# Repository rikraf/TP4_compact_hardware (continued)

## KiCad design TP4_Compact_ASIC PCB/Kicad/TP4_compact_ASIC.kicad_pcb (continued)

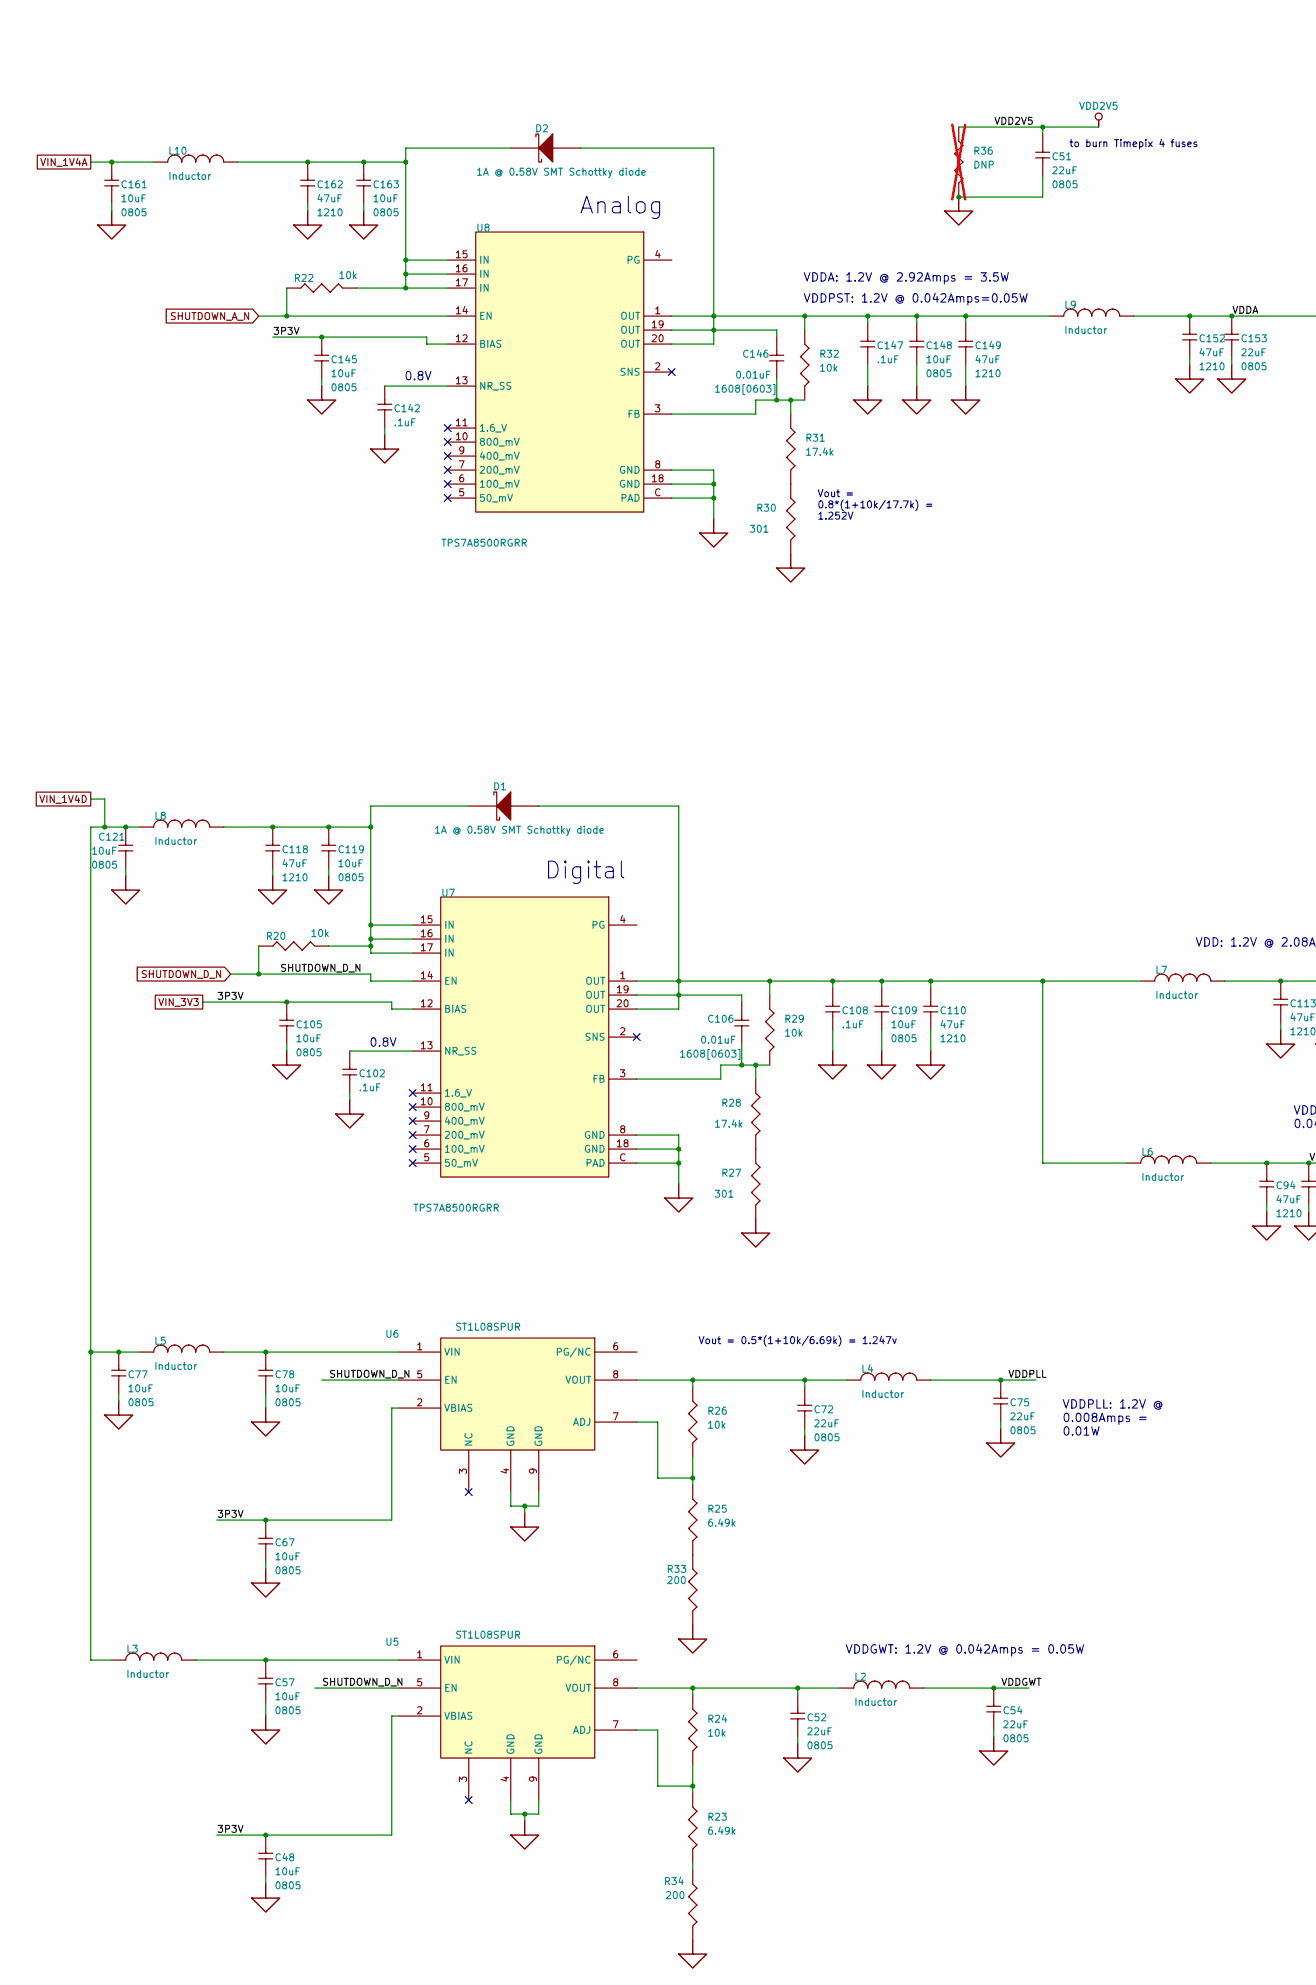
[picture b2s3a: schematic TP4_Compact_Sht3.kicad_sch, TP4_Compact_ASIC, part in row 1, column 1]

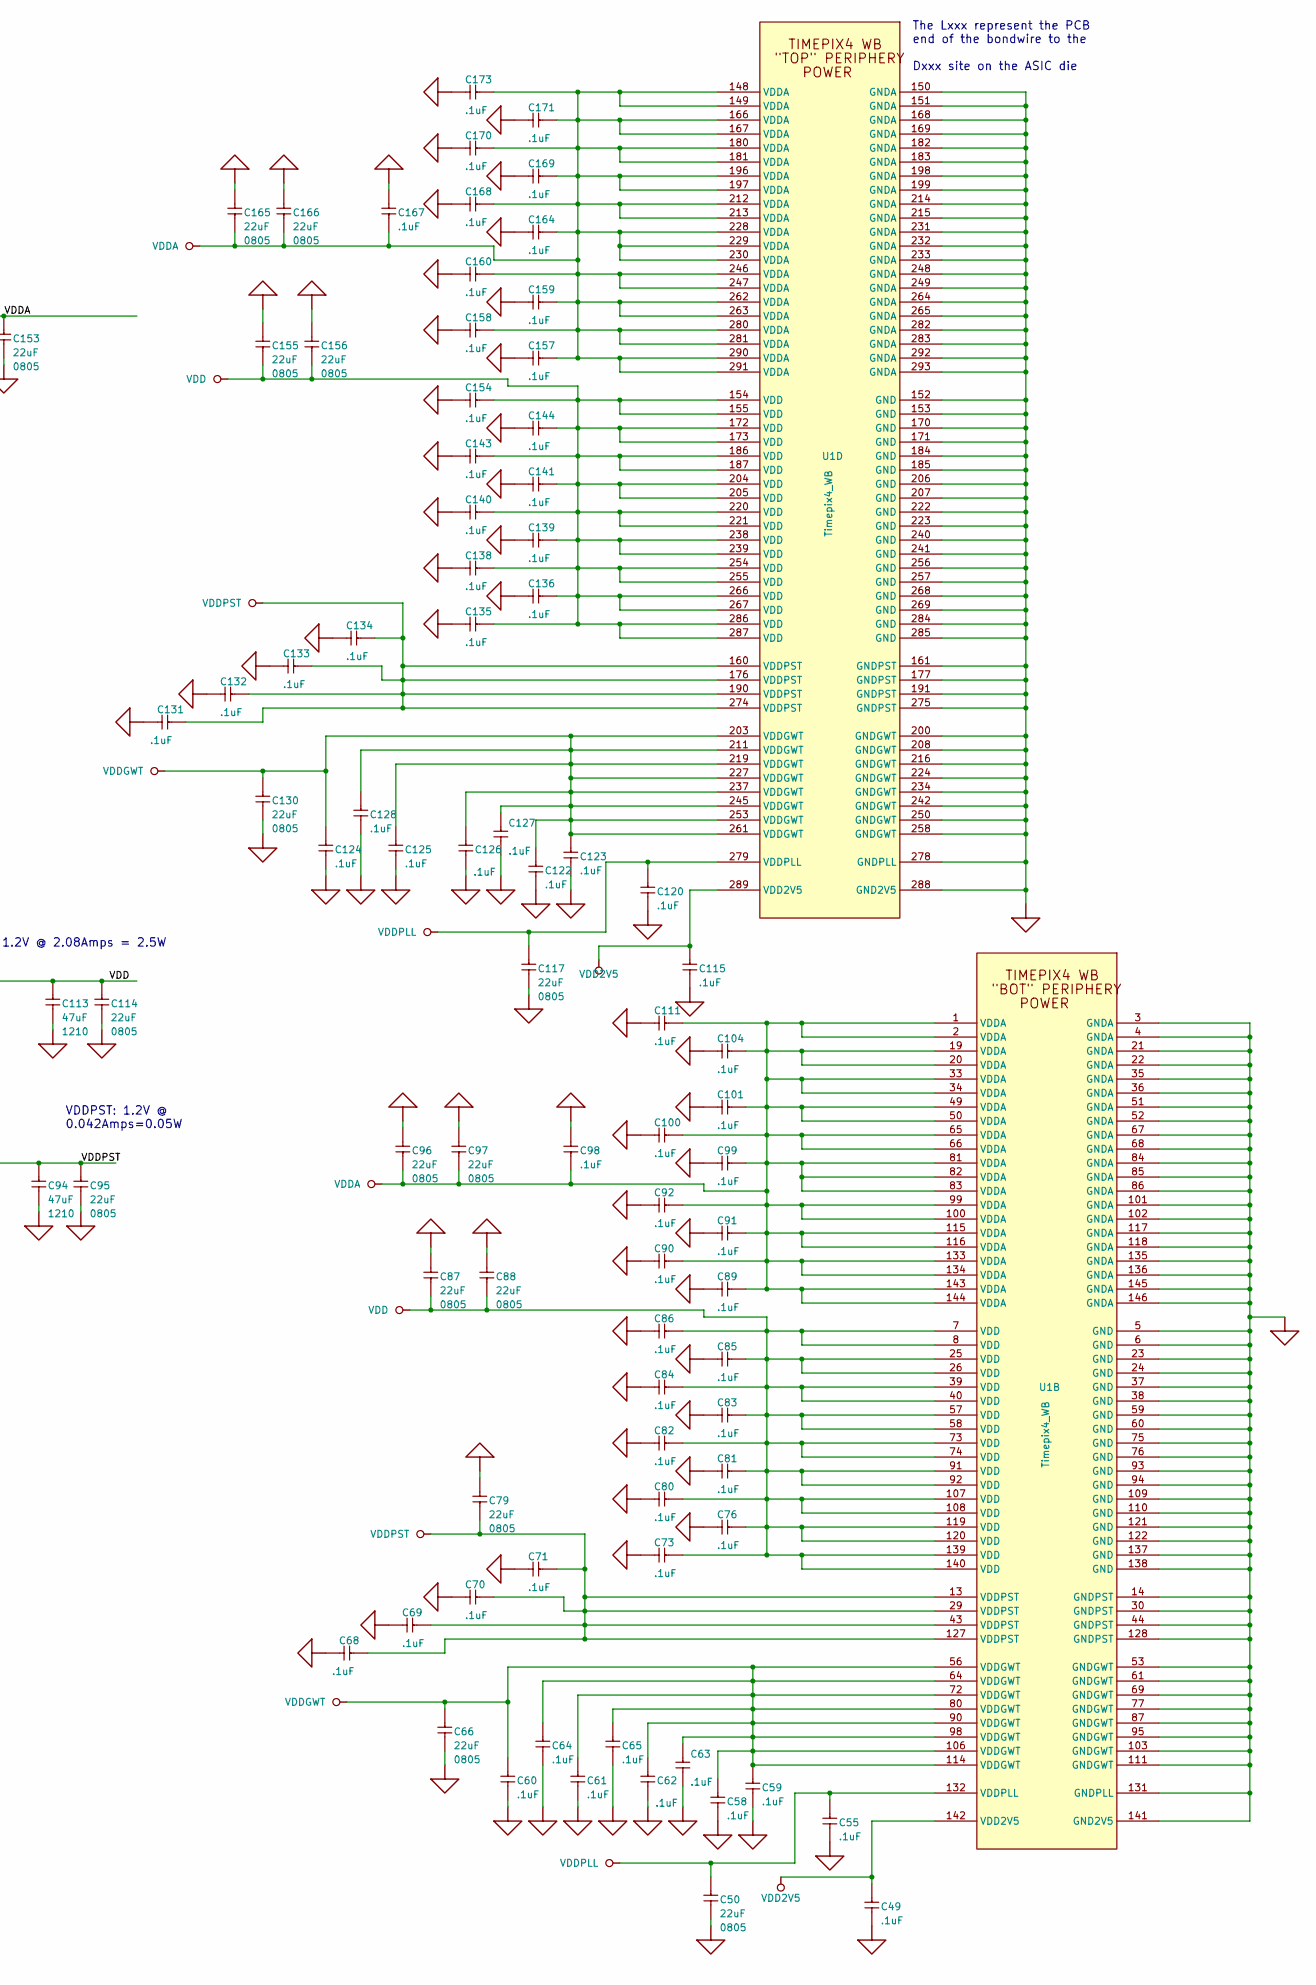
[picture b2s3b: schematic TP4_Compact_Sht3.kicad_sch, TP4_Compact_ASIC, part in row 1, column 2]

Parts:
C48, C57, C67, C77, C78, C105, C109, C119, C121, C145, C148, C161, C163: 10uF; C0805; VOLTAGE - RATED 10V; TOLERANCE ±10%; MANUFACTURER PART NUMBER GCM21BR70J106KE22L
C49, C55, C58, C59, C60, C61, C62, C63, C64, C65, C68, C69, C70, C71, C73, C76, C80, C81, C82, C83, C84, C85, C86, C89, C90, C91, C92, C98, C99, C100, C101, C102, C104, C108, C111, C115, C120, C122, C123, C124, C125, C126, C127, C128, C131, C132, C133, C134, C135, C136, C138, C139, C140, C141, C142, C143, C144, C147, C154, C157, C158, C159, C160, C164, C167, C168, C169, C170, C171, C173: .1uF; C_0201_0603Metric; VOLTAGE - RATED 6.3V; TOLERANCE ±10%; MANUFACTURER PART NUMBER GRM033R61A104ME15D
C50, C51, C52, C54, C66, C72, C75, C79, C87, C88, C95, C96, C97, C114, C117, C130, C153, C155, C156, C165, C166: 22uF; C0805; VOLTAGE - RATED 10V; TOLERANCE ±10%; MANUFACTURER PART NUMBER CL21X226MQQNNNG
C94, C110, C113, C118, C149, C152, C162: 47uF; C1210_M; VOLTAGE - RATED 10V; TOLERANCE ±10%; MANUFACTURER PART NUMBER GCM32ER70J476KE19L
C106, C146: 0.01uF; 1608[0603]; VOLTAGE - RATED 10V; TOLERANCE ±10%; MANUFACTURER PART NUMBER C0603C103K5RACTU
D1, D2: 1A @ 0.58V SMT Schottky diode; DO-219AD; MANUFACTURER PART NUMBER V1PM10-M3/H
L2, L3, L4, L5, L6, L7, L8, L9, L10: Inductor; L_0805_2012Metric; CURRENT RATING 4 Amps; MANUFACTURER PART NUMBER BLM21SP181BH1D
R20, R22, R24, R26, R29, R32: 10k; R_0402_1005Metric; MANUFACTURER PART NUMBER CR0402-FX-1002GLF
R23, R25: 6.49k; R_0402_1005Metric; MANUFACTURER PART NUMBER CR0402-FX-6491GLF
R27, R30: 301; R_0402_1005Metric; MANUFACTURER PART NUMBER CR0402-FX-3010GLF
R28, R31: 17.4k; R_0402_1005Metric; MANUFACTURER PART NUMBER CR0402-FX-1742GLF
R33, R34: 200; R_0402_1005Metric; MANUFACTURER PART NUMBER CR0402-FX-2000GLF
R36: DNP; R_0402_1005Metric; not fitted
U1: Timepix4_WB; Timepix4_WB_nocaps
U5, U6: ST1L08SPUR; DFN8_2X3_STM; MANUFACTURER_PART_NUMBER ST1L08PUR
U7, U8: TPS7A8500RGRR; RGR0020A; PARTNUMBER TPS7A8500RGRR

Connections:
GND: C48.2, C49.2, C50.2, C51.2, C52.2, C54.2, C55.2, C57.2, C58.2, C59.2, C60.2, C61.2, C62.2, C63.2, C64.2, C65.2, C66.2, C67.2, C68.2, C69.2, C70.2, C71.2, C72.2, C73.2, C75.2, C76.2, C77.2, C78.2, C79.2, C80.2, C81.2, C82.2, C83.2, C84.2, C85.2, C86.2, C87.2, C88.2, C89.2, C90.2, C91.2, C92.2, C94.2, C95.2, C96.2, C97.2, C98.2, C99.2, C100.2, C101.2, C102.2, C104.2, C105.2, C108.2, C109.2, C110.2, C111.2, C113.2, C114.2, C115.2, C117.2, C118.2, C119.2, C120.2, C121.2, C122.2, C123.2, C124.2, C125.2, C126.2, C127.2, C128.2, C130.2, C131.2, C132.2, C133.2, C134.2, C135.2, C136.2, C138.2, C139.2, C140.2, C141.2, C142.2, C143.2, C144.2, C145.2, C147.2, C148.2, C149.2, C152.2, C153.2, C154.2, C155.2, C156.2, C157.2, C158.2, C159.2, C160.2, C161.2, C162.2, C163.2, C164.2, C165.2, C166.2, C167.2, C168.2, C169.2, C170.2, C171.2, C173.2, R27.1, R30.1, R33.1, R34.1, R36.1, U1.3 (GNDA), U1.4 (GNDA), U1.5 (GND), U1.6 (GND), U1.14 (GNDPST), U1.21 (GNDA), U1.22 (GNDA), U1.23 (GND), U1.24 (GND), U1.30 (GNDPST), U1.35 (GNDA), U1.36 (GNDA), U1.37 (GND), U1.38 (GND), U1.44 (GNDPST), U1.51 (GNDA), U1.52 (GNDA), U1.53 (GNDGWT), U1.59 (GND), U1.60 (GND), U1.61 (GNDGWT), U1.67 (GNDA), U1.68 (GNDA), U1.69 (GNDGWT), U1.75 (GND), U1.76 (GND), U1.77 (GNDGWT), U1.84 (GNDA), U1.85 (GNDA), U1.86 (GNDA), U1.87 (GNDGWT), U1.93 (GND), U1.94 (GND), U1.95 (GNDGWT), U1.101 (GNDA), U1.102 (GNDA), U1.103 (GNDGWT), U1.109 (GND), U1.110 (GND), U1.111 (GNDGWT), U1.117 (GNDA), U1.118 (GNDA), U1.121 (GND), U1.122 (GND), U1.128 (GNDPST), U1.131 (GNDPLL), U1.135 (GNDA), U1.136 (GNDA), U1.137 (GND), U1.138 (GND), U1.141 (GND2V5), U1.145 (GNDA), U1.146 (GNDA), U1.150 (GNDA), U1.151 (GNDA), U1.152 (GND), U1.153 (GND), U1.161 (GNDPST), U1.168 (GNDA), U1.169 (GNDA), U1.170 (GND), U1.171 (GND), U1.177 (GNDPST), U1.182 (GNDA), U1.183 (GNDA), U1.184 (GND), U1.185 (GND), U1.191 (GNDPST), U1.198 (GNDA), U1.199 (GNDA), U1.200 (GNDGWT), U1.206 (GND), U1.207 (GND), U1.208 (GNDGWT), U1.214 (GNDA), U1.215 (GNDA), U1.216 (GNDGWT), U1.222 (GND), U1.223 (GND), U1.224 (GNDGWT), U1.231 (GNDA), U1.232 (GNDA), U1.233 (GNDA), U1.234 (GNDGWT), U1.240 (GND), U1.241 (GND), U1.242 (GNDGWT), U1.248 (GNDA), U1.249 (GNDA), U1.250 (GNDGWT), U1.256 (GND), U1.257 (GND), U1.258 (GNDGWT), U1.264 (GNDA), U1.265 (GNDA), U1.268 (GND), U1.269 (GND), U1.275 (GNDPST), U1.278 (GNDPLL), U1.282 (GNDA), U1.283 (GNDA), U1.284 (GND), U1.285 (GND), U1.288 (GND2V5), U1.292 (GNDA), U1.293 (GNDA), U5.4 (GND), U5.9 (GND), U6.4 (GND), U6.9 (GND), U7.8 (GND), U7.18 (GND), U7.C (PAD), U8.8 (GND), U8.18 (GND), U8.C (PAD); also elsewhere on the board
unnamed: C106.1, C108.1, C109.1, C110.1, D1.1 (A), L6.1, L7.1, R29.2, U7.1 (OUT), U7.19 (OUT), U7.20 (OUT)
unnamed: C118.1, C119.1, D1.2 (K), L8.2, R20.1, U7.15 (IN), U7.16 (IN), U7.17 (IN)
unnamed: C146.1, C147.1, C148.1, C149.1, D2.1 (A), L9.1, R32.2, U8.1 (OUT), U8.19 (OUT), U8.20 (OUT)
unnamed: C162.1, C163.1, D2.2 (K), L10.2, R22.1, U8.15 (IN), U8.16 (IN), U8.17 (IN)
unnamed: R23.1, R34.2
unnamed: R25.1, R33.2
unnamed: R27.2, R28.1
unnamed: R30.2, R31.1
unnamed: R23.2, R24.1, U5.7 (ADJ)
unnamed: C57.1, L3.2, U5.1 (VIN)
unnamed: C52.1, L2.1, R24.2, U5.8 (VOUT)
unnamed: R25.2, R26.1, U6.7 (ADJ)
unnamed: C78.1, L5.2, U6.1 (VIN)
unnamed: C72.1, L4.1, R26.2, U6.8 (VOUT)
unnamed: C106.2, R28.2, R29.1, U7.3 (FB)
unnamed: C102.1, U7.13 (NR_SS)
unnamed: C146.2, R31.2, R32.1, U8.3 (FB)
unnamed: C142.1, U8.13 (NR_SS)
SHUTDOWN_A_N: R22.2, U8.14 (EN); also elsewhere on the board
SHUTDOWN_D_N: R20.2, U5.5 (EN), U6.5 (EN), U7.14 (EN); also elsewhere on the board
VDD: C73.1, C76.1, C80.1, C81.1, C82.1, C83.1, C84.1, C85.1, C86.1, C87.1, C88.1, C113.1, C114.1, C135.1, C136.1, C138.1, C139.1, C140.1, C141.1, C143.1, C144.1, C154.1, C155.1, C156.1, L7.2, U1.7 (VDD), U1.8 (VDD), U1.25 (VDD), U1.26 (VDD), U1.39 (VDD), U1.40 (VDD), U1.57 (VDD), U1.58 (VDD), U1.73 (VDD), U1.74 (VDD), U1.91 (VDD), U1.92 (VDD), U1.107 (VDD), U1.108 (VDD), U1.119 (VDD), U1.120 (VDD), U1.139 (VDD), U1.140 (VDD), U1.154 (VDD), U1.155 (VDD), U1.172 (VDD), U1.173 (VDD), U1.186 (VDD), U1.187 (VDD), U1.204 (VDD), U1.205 (VDD), U1.220 (VDD), U1.221 (VDD), U1.238 (VDD), U1.239 (VDD), U1.254 (VDD), U1.255 (VDD), U1.266 (VDD), U1.267 (VDD), U1.286 (VDD), U1.287 (VDD)
VDD2V5: C49.1, C51.1, C115.1, R36.2, U1.142 (VDD2V5), U1.289 (VDD2V5)
VDDA: C89.1, C90.1, C91.1, C92.1, C96.1, C97.1, C98.1, C99.1, C100.1, C101.1, C104.1, C111.1, C152.1, C153.1, C157.1, C158.1, C159.1, C160.1, C164.1, C165.1, C166.1, C167.1, C168.1, C169.1, C170.1, C171.1, C173.1, L9.2, U1.1 (VDDA), U1.2 (VDDA), U1.19 (VDDA), U1.20 (VDDA), U1.33 (VDDA), U1.34 (VDDA), U1.49 (VDDA), U1.50 (VDDA), U1.65 (VDDA), U1.66 (VDDA), U1.81 (VDDA), U1.82 (VDDA), U1.83 (VDDA), U1.99 (VDDA), U1.100 (VDDA), U1.115 (VDDA), U1.116 (VDDA), U1.133 (VDDA), U1.134 (VDDA), U1.143 (VDDA), U1.144 (VDDA), U1.148 (VDDA), U1.149 (VDDA), U1.166 (VDDA), U1.167 (VDDA), U1.180 (VDDA), U1.181 (VDDA), U1.196 (VDDA), U1.197 (VDDA), U1.212 (VDDA), U1.213 (VDDA), U1.228 (VDDA), U1.229 (VDDA), U1.230 (VDDA), U1.246 (VDDA), U1.247 (VDDA), U1.262 (VDDA), U1.263 (VDDA), U1.280 (VDDA), U1.281 (VDDA), U1.290 (VDDA), U1.291 (VDDA)
VDDGWT: C54.1, C58.1, C59.1, C60.1, C61.1, C62.1, C63.1, C64.1, C65.1, C66.1, C122.1, C123.1, C124.1, C125.1, C126.1, C127.1, C128.1, C130.1, L2.2, U1.56 (VDDGWT), U1.64 (VDDGWT), U1.72 (VDDGWT), U1.80 (VDDGWT), U1.90 (VDDGWT), U1.98 (VDDGWT), U1.106 (VDDGWT), U1.114 (VDDGWT), U1.203 (VDDGWT), U1.211 (VDDGWT), U1.219 (VDDGWT), U1.227 (VDDGWT), U1.237 (VDDGWT), U1.245 (VDDGWT), U1.253 (VDDGWT), U1.261 (VDDGWT)
VDDPLL: C50.1, C55.1, C75.1, C117.1, C120.1, L4.2, U1.132 (VDDPLL), U1.279 (VDDPLL)
VDDPST: C68.1, C69.1, C70.1, C71.1, C79.1, C94.1, C95.1, C131.1, C132.1, C133.1, C134.1, L6.2, U1.13 (VDDPST), U1.29 (VDDPST), U1.43 (VDDPST), U1.127 (VDDPST), U1.160 (VDDPST), U1.176 (VDDPST), U1.190 (VDDPST), U1.274 (VDDPST)
VIN_1V4A: C161.1, L10.1; also elsewhere on the board
VIN_1V4D: C77.1, C121.1, L3.1, L5.1, L8.1; also elsewhere on the board
VIN_3V3: C48.1, C67.1, C105.1, C145.1, U5.2 (VBIAS), U6.2 (VBIAS), U7.12 (BIAS), U8.12 (BIAS); also elsewhere on the board

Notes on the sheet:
Vout = 0.8*(1+10k/17.7k) = 1.252V
VDDPST: 1.2V @ 0.042Amps=0.05W
The Lxxx represent the PCB end of the bondwire to the Dxxx site on the ASIC die
Analog
VDDA: 1.2V @ 2.92Amps = 3.5W
Digital
VDDPST: 1.2V @ 0.042Amps=0.05W
to burn Timepix 4 fuses
0.8V
VDD: 1.2V @ 2.08Amps = 2.5W
Vout = 0.5*(1+10k/6.69k) = 1.247v
VDDPLL: 1.2V @ 0.008Amps = 0.01W
0.8V
VDDGWT: 1.2V @ 0.042Amps = 0.05W

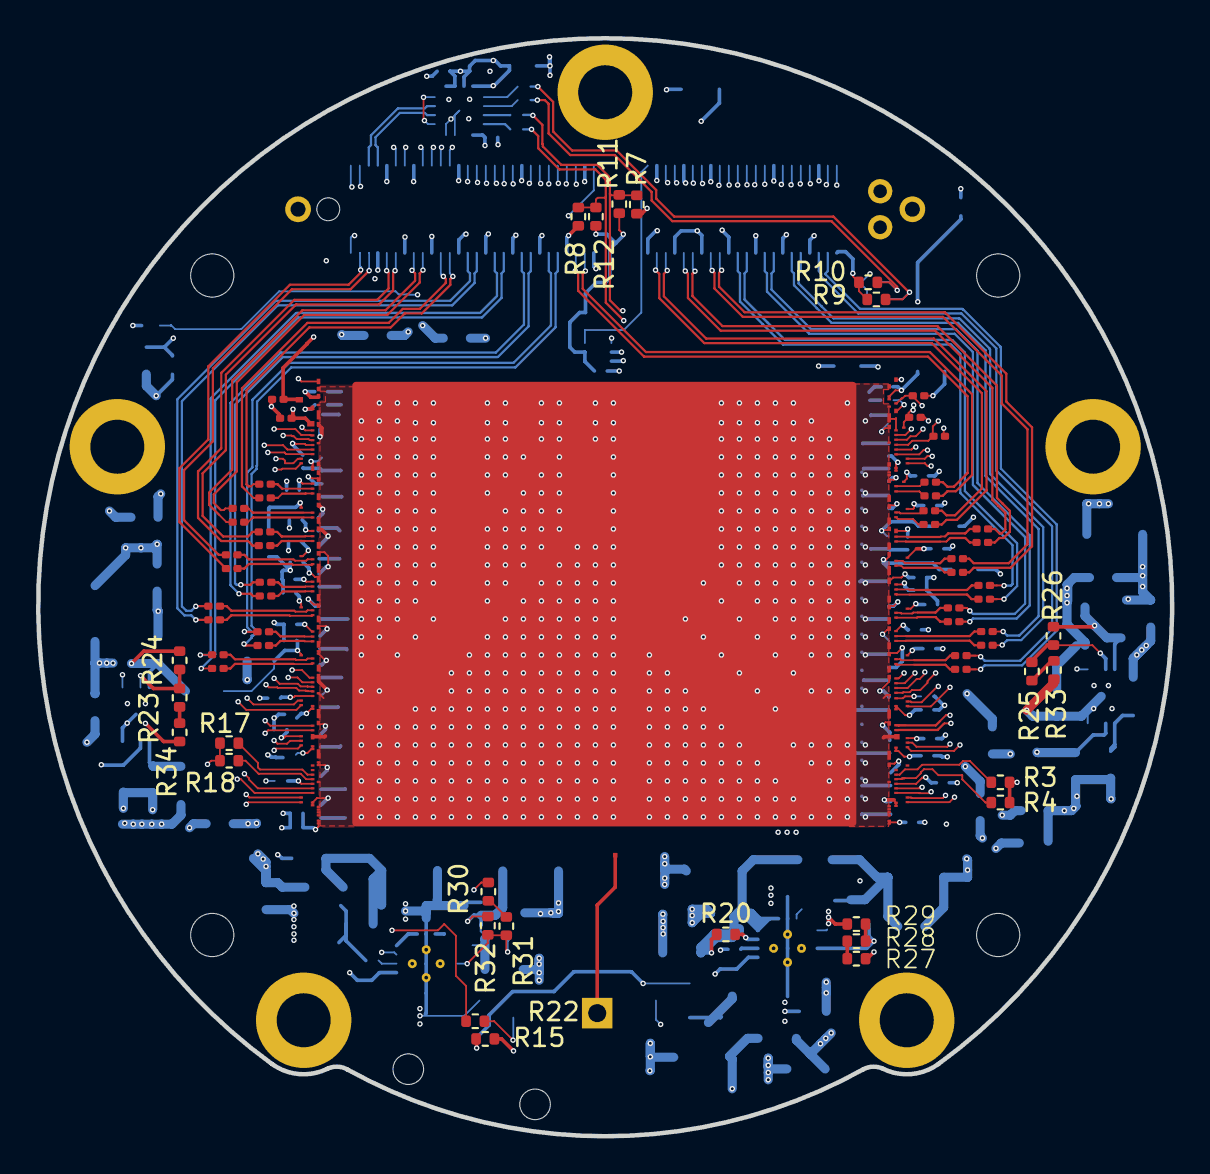
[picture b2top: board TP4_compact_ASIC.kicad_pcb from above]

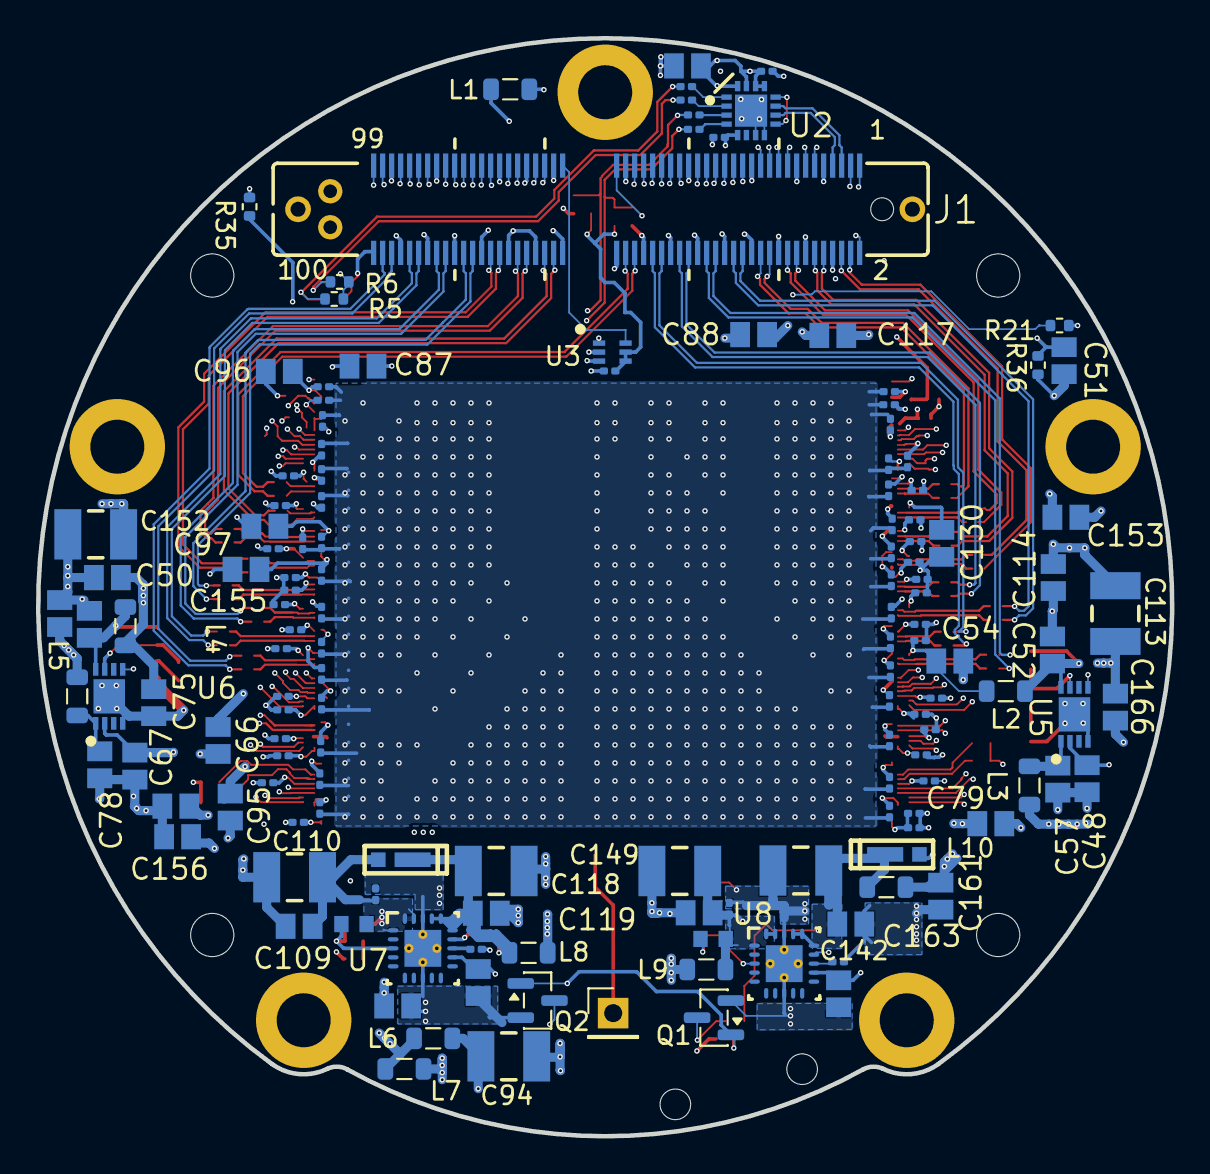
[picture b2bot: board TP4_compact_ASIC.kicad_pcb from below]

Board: 8 copper layers, 63.0 x 61.0 mm, 218 parts (143 on the bottom side), 152 nets.

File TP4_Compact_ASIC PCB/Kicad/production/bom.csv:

Designator,Footprint,Quantity,Value,LCSC Part #
"C1, C10, C100, C101, C102, C104, C108, C11, C111, C115, C12, C120, C122, C123, C124, C125, C126, C127, C128, C13, C131, C132, C133, C134, C135, C136, C138, C139, C14, C140, C141, C142, C143, C144, C147, C15, C154, C157, C158, C159, C16, C160, C164, C167, C168, C169, C170, C171, C173, C18, C2, C20, C22, C23, C26, C27, C28, C3, C30, C31, C32, C33, C34, C35, C36, C37, C38, C39, C4, C40, C41, C42, C43, C44, C45, C49, C5, C55, C58, C59, C6, C60, C61, C62, C63, C64, C65, C68, C69, C7, C70, C71, C73, C76, C8, C80, C81, C82, C83, C84, C85, C86, C89, C9, C90, C91, C92, C98, C99",0201,109,.1uF,
"C105, C109, C119, C121, C145, C148, C161, C163, C48, C57, C67, C77, C78",C0805,13,10uF,
"C106, C146",1608[0603],2,0.01uF,
"C110, C113, C118, C149, C152, C162, C94",C1210_M,7,47uF,
"C114, C117, C130, C153, C155, C156, C165, C166, C29, C50, C51, C52, C54, C66, C72, C75, C79, C87, C88, C95, C96, C97",C0805,22,22uF,
"D1, D2",DO-219AD,2,1A @ 0.58V SMT Schottky diode,
J1,MEC5-050-01-L-DV-W1-K-TR,1,MEC5-050-01-L-DV-W1-K-TR,
"L1, L10, L2, L3, L4, L5, L6, L7, L8, L9",0805,10,Inductor,
"Q1, Q2",SOT-23,2,SI2302-TP,
"R10, R11, R12, R15, R17, R18, R20, R22, R24, R26, R29, R3, R32, R4, R9",0402,15,10k,
"R23, R25",0402,2,6.49k,
"R27, R30",0402,2,301,
"R28, R31",0402,2,17.4k,
"R33, R34",0402,2,200,
"R5, R6, R7, R8",0402,4,2k,
U2,QFN16_3x3_mm,1,NB6N11SMNG,
U3,DRL6,1,TMP102AIDRLR,
"U5, U6",DFN8_2X3_STM,2,ST1L08SPUR,
"U7, U8",RGR0020A,2,TPS7A8500RGRR,

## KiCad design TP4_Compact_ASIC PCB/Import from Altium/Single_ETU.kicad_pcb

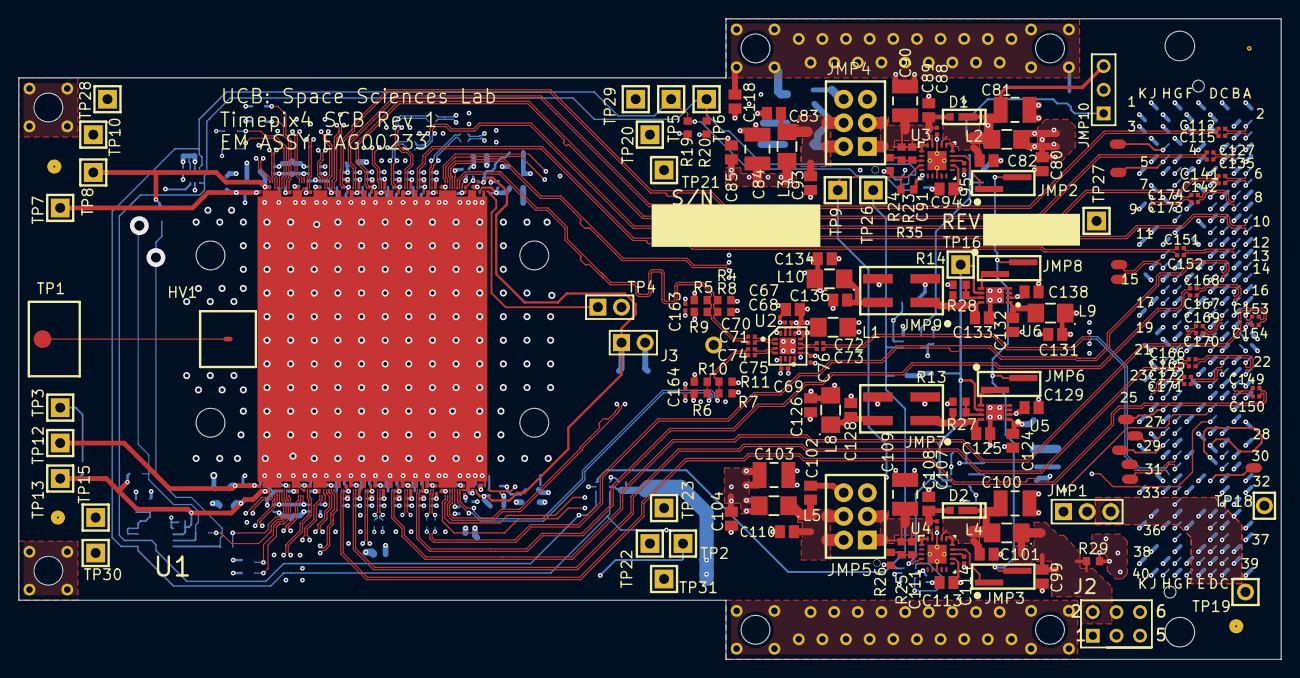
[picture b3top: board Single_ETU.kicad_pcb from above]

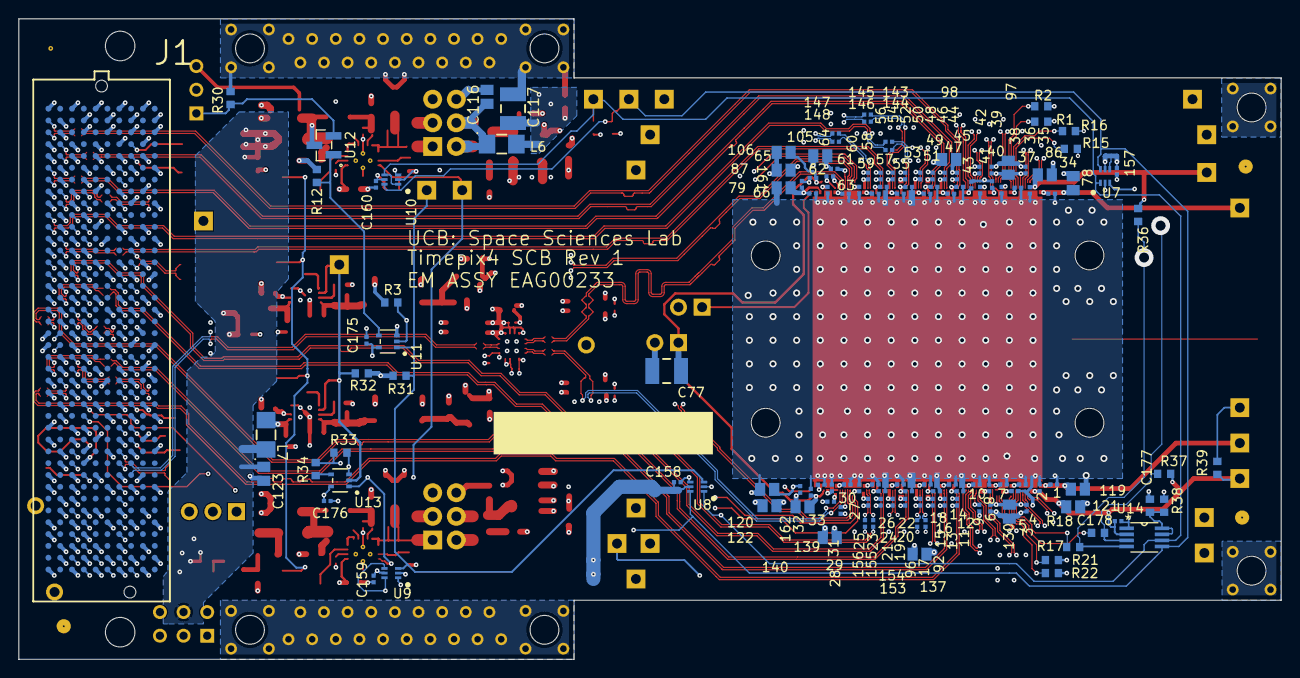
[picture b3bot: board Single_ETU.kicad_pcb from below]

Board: 10 copper layers, 135.7 x 68.8 mm, 283 parts (136 on the bottom side), 175 nets.

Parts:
C1, C2, C3, C4, C5, C6, C7, C8, C9, C10, C11, C12, C13, C14, C15, C16, C17, C18, C19, C20, C21, C22, C23, C24, C25, C26, C27, C28, C29, C30, C31, C32, C33, C34, C35, C36, C37, C38, C39, C40, C41, C42, C43, C44, C45, C46, C47, C48, C49, C50, C51, C52, C53, C54, C55, C56, C57, C58, C59, C60, C61, C62, C63, C64, C65, C66, C68, C69, C70, C71, C72, C73, C74, C75, C76, C88, C92, C95, C96, C107, C112, C114, C115, C127, C135, C141, C142, C143, C144, C145, C146, C147, C148, C149, C150, C151, C152, C153, C154, C155, C156, C157, C158, C159, C160, C161, C162, C163, C164, C165, C166, C167, C168, C169, C170, C171, C172, C173, C174, C175, C176, C178: ${1UF}; CAP_0201
C67, C78, C79, C83, C85, C86, C87, C97, C98, C102, C104, C105, C106, C116, C118, C119, C120, C121, C122, C126, C128, C130, C134, C136, C137, C139, C140: 22uF; C0805
C77, C81, C84, C90, C100, C103, C109, C117: 47uF; C1210_M
C80, C82, C89, C93, C94, C99, C101, C108, C110, C113, C123, C124, C125, C129, C131, C132, C133, C138: 10uF; C0805
C91, C111: 0.01uF; 1608[0603]
C177: 100pF; 1608[0603]
D1, D2: 1A @ 0.58V SMT Schottky diode; DO-219AD
HV1: HV_bond_pad; HV_BOND_PAD
J1: MC-HPC-10; ASP-134488-01
J2: Header 3X2; HDR2X3
J3: Header 2; HDR1X2
JMP1, JMP10: Header 3; HDR1X3
JMP2, JMP6, JMP8: 0.050" Header 2; HDR_1X2_SMT_050
JMP3: 0.050: Header 2; HDR_1X2_SMT_050
JMP4, JMP5: Header 3X2; HDR_2x3
JMP7, JMP9: Header 2X2 SMT; HDR_2X2_SMT
L1, L2, L3, L4, L5, L6, L7, L8, L9, L10: Inductor; IND_1206
R1, R2, R21, R22: 1k 1%; 1608[0603]
R3, R12, R13, R14, R30, R31, R32, R33, R34: 4.7k; 1608[0603]
R4, R5, R6, R7, R19, R20, R35, R36, R37: 10k; 1608[0603]
R8, R9, R10, R11: 2k; 1608[0603]
R15, R16, R17, R18: 0 OHMS; 1608[0603]
R23, R25: 12.4k; 1608[0603]
R24, R26: 24.9k; 1608[0603]
R27, R28: 8.2k; 1608[0603]
R29: zero; 1608[0603]
R38: 200k OHMS; 1608[0603]
R39: 160k; 1608[0603]
TP1: surface mount TP; HV_solder_pad
TP2, TP3, TP5, TP6, TP7, TP8, TP9, TP10, TP12, TP13, TP15, TP16, TP18, TP19, TP20, TP21, TP22, TP23, TP26, TP27, TP28, TP29, TP30, TP31: TP
TP4: Header 2; HDR1X2
U1: Timepix4_WB; Timepix4_WB_bands
U2: NB6N11SMNG; QFN16_3x3_mm
U3, U4: TPS7A8500RGRR; RGR0020A
U5, U6: ST1L08SPUR; DFN8_2X3_STM
U7, U8, U9, U10: TMP102AIDRLR; DRL6
U11, U13: NC7SZ08P5X; SC70-5_ONS-L
U12: BSS123; SOT23-3_ONS-M
U14: PCA9306DCTRE4; DCT8

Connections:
3P3V: C94.1, C113.1, C129.1, C138.1, C157.1, C158.1, C159.1, C160.1, C175.1, C176.1, JMP1.2, L1.1, R19.1, R20.1, R31.2, R32.1, R35.2, R38.1, U3.12, U4.12, U5.2, U6.2, U7.4, U7.5, U8.5, U9.5, U10.5, U11.5, U13.5
12P0V: J1.C35, J1.C37, TP18.1
B_N: C75.1, U2.4
B_P: C74.1, U2.3
CLK_REF_B_N: C75.2, R7.1, R11.2, U1.130
CLK_REF_B_P: C74.2, R6.1, R10.2, U1.129
CLK_REF_T_N: C71.2, R5.1, R9.2, U1.277
CLK_REF_T_P: C70.2, R4.1, R8.2, U1.276
DAC_OUT_B: TP2.1, U1.147
DAC_OUT_T: TP4.1, U1.294
DIGITALPIXEL0_B: J1.D26, U1.123
DIGITALPIXEL0_T: J1.D23, U1.270
DIGITALPIXEL1_B: J1.D27, U1.124
DIGITALPIXEL1_T: J1.D24, U1.271
FMC_3P3V: J1.C39, J1.D36, J1.D38, J1.D40, JMP1.3
GND: C1.2, C2.2, C3.2, C4.2, C5.2, C6.2, C7.2, C8.2, C9.2, C10.2, C11.2, C12.2, C13.2, C14.2, C15.2, C16.2, C17.2, C18.2, C19.2, C20.2, C21.2, C22.2, C23.2, C24.2, C25.2, C26.2, C27.2, C28.2, C29.2, C30.2, C31.2, C32.2, C33.2, C34.2, C35.2, C36.2, C37.2, C38.2, C39.2, C40.2, C41.2, C42.2, C43.2, C44.2, C45.2, C46.2, C47.2, C48.2, C49.2, C50.2, C51.2, C52.2, C53.2, C54.2, C55.2, C56.2, C57.2, C58.2, C59.2, C60.2, C61.2, C62.2, C63.2, C64.2, C65.2, C66.2, C67.2, C68.2, C69.2, C76.2, C77.2, C78.2, C79.2, C80.2, C81.2, C82.2, C83.2, C84.2, C85.2, C86.2, C87.2, C88.2, C89.2, C90.2, C93.2, C94.2, C95.2, C97.2, C98.2, C99.2, C100.2, C101.2, C102.2, C103.2, C104.2, C105.2, C106.2, C107.2, C108.2, C109.2, C110.2, C113.2, C114.2, C116.2, C117.2, C118.2, C119.2, C120.2, C121.2, C122.2, C123.2, C124.2, C125.2, C126.2, C128.2, C129.2, C130.2, C131.2, C132.2, C133.2, C134.2, C136.2, C137.2, C138.2, C139.2, C140.2, C157.2, C158.2, C159.2, C160.2, C161.2, C162.2, C163.2, C164.2, C175.2, C176.2, C177.2, C178.2, J1.A1, J1.A4, J1.A5, J1.A8, J1.A9, J1.A12, J1.A13, J1.A16, J1.A17, J1.A20, J1.A21, J1.A24, J1.A25, J1.A28, J1.A29, J1.A32, J1.A33, J1.A36, J1.A37, J1.A40, J1.B2, J1.B3, J1.B6, J1.B7, J1.B10, J1.B11, J1.B14, J1.B15, J1.B18, J1.B19, J1.B22, J1.B23, J1.B26, J1.B27, J1.B30, J1.B31, J1.B34, J1.B35, J1.B38, J1.B39, J1.C1, J1.C4, J1.C5, J1.C8, J1.C9, J1.C12, J1.C13, J1.C16, J1.C17, J1.C20, J1.C21, J1.C24, J1.C25, J1.C28, J1.C29, J1.C32, J1.C33, J1.C34, J1.C36, J1.C38, J1.C40, J1.D2, J1.D3, J1.D6, J1.D7, J1.D10, J1.D13, J1.D16, J1.D19, J1.D22, J1.D25, J1.D28, J1.D35, J1.D37, J1.D39, J1.E1, J1.E4, J1.E5, J1.E8, J1.E11, J1.E14, J1.E17, J1.E20, J1.E23, J1.E26, J1.E29, J1.E32, J1.E35, J1.E38, J1.E40, J1.F2, J1.F3, J1.F6, J1.F9, J1.F12, J1.F15, J1.F18, J1.F21, J1.F24, J1.F27, J1.F30, J1.F33, J1.F36, J1.F39, J1.G1, J1.G4, J1.G5, J1.G8, J1.G11, J1.G14, J1.G17, J1.G20, J1.G23, J1.G26, J1.G29, J1.G32, J1.G35, J1.G38, J1.G40, J1.H2, J1.H3, J1.H6, J1.H9, J1.H12, J1.H15, J1.H18, J1.H21, J1.H24, J1.H27, J1.H30, J1.H33, J1.H36, J1.H39, J1.J1, J1.J4, J1.J5, J1.J8, J1.J11, J1.J14, J1.J17, J1.J20, J1.J23, J1.J26, J1.J29, J1.J32, J1.J35, J1.J38, J1.J40, J1.K2, J1.K3, J1.K6, J1.K9, J1.K12, J1.K15, J1.K18, J1.K21, J1.K24, J1.K27, J1.K30, J1.K33, J1.K36, J1.K39, J2.1, J2.3, J2.5, J3.2, JMP4.5, JMP4.6, JMP5.5, JMP5.6, JMP7.3, JMP7.4, JMP9.3, JMP9.4, R1.1, R2.1, R3.1, R8.1, R9.1, R10.1, R11.1, R12.1, R13.1, R14.1, R21.1, R22.1, R24.1, R26.1, R30.1, R33.1, R39.2, TP3.1, TP4.2, TP27.1, TP28.1, TP29.1, TP30.1, TP31.1, U1.3, U1.4, U1.5, U1.6, U1.14, U1.21, U1.22, U1.23, U1.24, U1.30, U1.35, U1.36, U1.37, U1.38, U1.44, U1.51, U1.52, U1.53, U1.59, U1.60, U1.61, U1.67, U1.68, U1.69, U1.75, U1.76, U1.77, U1.84, U1.85, U1.86, U1.87, U1.93, U1.94, U1.95, U1.101, U1.102, U1.103, U1.109, U1.110, U1.111, U1.117, U1.118, U1.121, U1.122, U1.128, U1.131, U1.135, U1.136, U1.137, U1.138, U1.141, U1.145, U1.146, U1.150, U1.151, U1.152, U1.153, U1.161, U1.168, U1.169, U1.170, U1.171, U1.177, U1.182, U1.183, U1.184, U1.185, U1.191, U1.198, U1.199, U1.200, U1.206, U1.207, U1.208, U1.214, U1.215, U1.216, U1.222, U1.223, U1.224, U1.231, U1.232, U1.233, U1.234, U1.240, U1.241, U1.242, U1.248, U1.249, U1.250, U1.256, U1.257, U1.258, U1.264, U1.265, U1.268, U1.269, U1.275, U1.278, U1.282, U1.283, U1.284, U1.285, U1.288, U1.292, U1.293, U2.7, U2.8, U2.17, U3.8, U3.18, U3.21, U3.V, U4.8, U4.18, U4.C, U4.V, U5.4, U5.9, U6.4, U6.9, U7.2, U8.2, U8.4, U9.2, U10.2, U11.3, U13.3, U14.1
HIGH_I_PG: R35.1, TP9.1, U3.4, U4.4, U13.1
I2C_SCL: J1.C30, R20.2, TP6.1, U7.1, U8.1, U9.1, U10.1, U10.4, U14.6
I2C_SCL_1p2: R16.1, R18.1, R37.2, U14.3
I2C_SCL_B: R18.2, U1.16
I2C_SCL_T: R16.2, U1.163
I2C_SDA: J1.C31, R19.2, TP5.1, U7.6, U8.6, U9.4, U9.6, U10.6, U14.5
I2C_SDA_1p2: R15.1, R17.1, R36.2, U14.4
I2C_SDA_B: R17.2, U1.15
I2C_SDA_T: R15.2, U1.162
IN_N: C73.2, U2.10
IN_P: C72.2, U2.11
LDO_ENABLE: JMP2.2, JMP3.2, JMP6.2, JMP8.2, JMP10.2
LOW_I_PG: R32.2, TP16.1, U5.6, U6.6, U13.2
NetC95_1: C95.1, U3.13
NetC114_1: C114.1, U4.13
NetR1_2: R1.2, U1.164
NetR2_2: R2.2, U1.165
NetR12_2: R12.2, U11.4, U12.G
NetR21_2: R21.2, U1.17
NetR22_2: R22.2, U1.18
NetR34_2: R34.2, U13.4
OVERTEMP_N: R31.1, TP26.1, U7.3, U8.3, U9.3, U10.3, U11.1
PG: J1.H29, R33.2, R34.1
PWR_EN: J1.H25, R3.2, U11.2
RAW_LDO_ENABLE: JMP10.1, R30.2, U12.S
RESET_B_N: J1.D15, U1.48
RESET_B_P: J1.D14, U1.47
RESET_T_N: J1.G16, U1.195
RESET_T_P: J1.G15, U1.194
S0B_N: C150.1, U1.55
S0B_P: C149.1, U1.54
S0T_N: C115.1, U1.202
S0T_P: C112.1, U1.201
S1B_N: C166.1, U1.63
S1B_P: C165.1, U1.62
S1T_N: C135.1, U1.210
S1T_P: C127.1, U1.209
S2B_N: C171.1, U1.71
S2B_P: C172.1, U1.70
S2T_N: C142.1, U1.218
S2T_P: C141.1, U1.217
S3B_N: C96.1, U1.79
S3B_P: C92.1, U1.78
S3T_N: C173.1, U1.226
S3T_P: C174.1, U1.225
S4B_N: C154.1, U1.89
S4B_P: C153.1, U1.88
S4T_N: C144.1, U1.236
S4T_P: C143.1, U1.235
S5B_N: C170.1, U1.97
S5B_P: C169.1, U1.96
S5T_N: C146.1, U1.244
S5T_P: C145.1, U1.243
S6B_N: C168.1, U1.105
S6B_P: C167.1, U1.104
S6T_N: C152.1, U1.252
S6T_P: C151.1, U1.251
S7B_N: C156.1, U1.113
S7B_P: C155.1, U1.112
S7T_N: C148.1, U1.260
S7T_P: C147.1, U1.259
SC_CLOCK_IN_B_N: J1.D9, U1.10
SC_CLOCK_IN_B_P: J1.D8, U1.9
SC_CLOCK_IN_T_N: J1.G37, U1.157
SC_CLOCK_IN_T_P: J1.G36, U1.156
SC_CLOCK_OUT_B_N: J1.G7, U1.32
SC_CLOCK_OUT_B_P: J1.G6, U1.31
SC_CLOCK_OUT_T_N: J1.H23, U1.179
SC_CLOCK_OUT_T_P: J1.H22, U1.178
SC_DATA_IN_B_N: J1.D11, U1.11
SC_DATA_IN_B_P: J1.D12, U1.12
SC_DATA_IN_T_N: J1.G34, U1.159
SC_DATA_IN_T_P: J1.G33, U1.158
SC_DATA_OUT_B_N: J1.G10, U1.28
SC_DATA_OUT_B_P: J1.G9, U1.27
SC_DATA_OUT_T_N: J1.G28, U1.175
SC_DATA_OUT_T_P: J1.G27, U1.174
SERIAL_OUT0_B_N: C150.2, J1.B25
SERIAL_OUT0_B_P: C149.2, J1.B24
SERIAL_OUT0_T_N: C115.2, J1.A3
SERIAL_OUT0_T_P: C112.2, J1.A2
SERIAL_OUT1_B_N: C166.2, J1.A23
SERIAL_OUT1_B_P: C165.2, J1.A22
SERIAL_OUT1_T_N: C135.2, J1.B5
SERIAL_OUT1_T_P: C127.2, J1.B4
SERIAL_OUT2_B_N: C171.2, J1.C23
SERIAL_OUT2_B_P: C172.2, J1.C22
SERIAL_OUT2_T_N: C142.2, J1.A7
SERIAL_OUT2_T_P: C141.2, J1.A6
SERIAL_OUT3_B_N: C96.2, J1.B21
SERIAL_OUT3_B_P: C92.2, J1.B20
SERIAL_OUT3_T_N: C173.2, J1.B9
SERIAL_OUT3_T_P: C174.2, J1.B8
SERIAL_OUT4_B_N: C154.2, J1.A19
SERIAL_OUT4_B_P: C153.2, J1.A18
SERIAL_OUT4_T_N: C144.2, J1.A11
SERIAL_OUT4_T_P: C143.2, J1.A10
SERIAL_OUT5_B_N: C170.2, J1.C19
SERIAL_OUT5_B_P: C169.2, J1.C18
SERIAL_OUT5_T_N: C146.2, J1.C11
SERIAL_OUT5_T_P: C145.2, J1.C10
SERIAL_OUT6_B_N: C168.2, J1.B17
SERIAL_OUT6_B_P: C167.2, J1.B16
SERIAL_OUT6_T_N: C152.2, J1.B13
SERIAL_OUT6_T_P: C151.2, J1.B12
SERIAL_OUT7_B_N: C156.2, J1.C15
SERIAL_OUT7_B_P: C155.2, J1.C14
SERIAL_OUT7_T_N: C148.2, J1.A15
SERIAL_OUT7_T_P: C147.2, J1.A14
SHUTTER_B_N: J1.D18, U1.42
SHUTTER_B_P: J1.D17, U1.41
SHUTTER_T_N: J1.G22, U1.189
SHUTTER_T_P: J1.G21, U1.188
TDI_TDO: J1.D30, J1.D31
TESTOUT_B_N: J1.G25, U1.126
TESTOUT_B_P: J1.G24, U1.125
TESTOUT_T_N: J1.H17, U1.273
TESTOUT_T_P: J1.H16, U1.272
TO_SYNC_B_N: J1.D21, U1.46
TO_SYNC_B_P: J1.D20, U1.45
TO_SYNC_T_N: J1.G19, U1.193
TO_SYNC_T_P: J1.G18, U1.192
TPX4_RefClk_N: C73.1, J1.H32
TPX4_RefClk_P: C72.1, J1.H31
T_N: C71.1, U2.2
T_P: C70.1, U2.1
U3_EN: JMP2.1, U3.14
U3_FB: C91.2, R23.1, R24.2, U3.3
U4_EN: JMP3.1, U4.14
U4_FB: C111.2, R25.1, R26.2, U4.3
U5_ADJ: R13.2, R27.1, U5.7
U5_EN: JMP6.1, U5.5
U6_ADJ: R14.2, R28.1, U6.7
U6_EN: JMP8.1, U6.5
U14_VREF2: C177.1, R38.2, U14.7, U14.8
VADJ: J1.E39, J1.F40, J1.G39, J1.H40, TP19.1
VCC_33_U2: C67.1, C68.1, C69.1, C76.1, C163.1, C164.1, L1.2, R4.2, R5.2, R6.2, R7.2, U2.5, U2.9, U2.12, U2.13, U2.14, U2.15, U2.16
VDD: C2.1, C5.1, C8.1, C12.1, C16.1, C20.1, C24.1, C27.1, C31.1, C35.1, C38.1, C41.1, C45.1, C49.1, C53.1, C57.1, C60.1, C64.1, C84.1, C85.1, C86.1, C87.1, C121.1, C122.1, C178.1, L3.2, R36.1, R37.1, R39.1, TP8.1, TP13.1, U1.7, U1.8, U1.25, U1.26, U1.39, U1.40, U1.57, U1.58, U1.73, U1.74, U1.91, U1.92, U1.107, U1.108, U1.119, U1.120, U1.139, U1.140, U1.154, U1.155, U1.172, U1.173, U1.186, U1.187, U1.204, U1.205, U1.220, U1.221, U1.238, U1.239, U1.254, U1.255, U1.266, U1.267, U1.286, U1.287, U14.2
VDD2V5: C32.1, C65.1, C77.1, C106.1, C140.1, J3.1, U1.142, U1.289
VDDA: C1.1, C4.1, C7.1, C10.1, C14.1, C18.1, C22.1, C26.1, C30.1, C33.1, C34.1, C37.1, C40.1, C43.1, C47.1, C51.1, C55.1, C59.1, C63.1, C66.1, C78.1, C79.1, C103.1, C104.1, C119.1, C120.1, C161.1, C162.1, L5.2, TP7.1, TP12.1, U1.1, U1.2, U1.19, U1.20, U1.33, U1.34, U1.49, U1.50, U1.65, U1.66, U1.81, U1.82, U1.83, U1.99, U1.100, U1.115, U1.116, U1.133, U1.134, U1.143, U1.144, U1.148, U1.149, U1.166, U1.167, U1.180, U1.181, U1.196, U1.197, U1.212, U1.213, U1.228, U1.229, U1.230, U1.246, U1.247, U1.262, U1.263, U1.280, U1.281, U1.290, U1.291
VDDA_RAW: C102.1, C110.1, JMP5.2, JMP5.4, L5.1
VDDA_U4: C107.1, C108.1, C109.1, C111.1, D2.1, JMP5.1, JMP5.3, R25.2, U4.1, U4.19, U4.20
VDDGWT: C11.1, C13.1, C15.1, C17.1, C19.1, C21.1, C23.1, C25.1, C44.1, C46.1, C48.1, C50.1, C52.1, C54.1, C56.1, C58.1, C98.1, C134.1, C137.1, L10.2, TP20.1, TP22.1, U1.56, U1.64, U1.72, U1.80, U1.90, U1.98, U1.106, U1.114, U1.203, U1.211, U1.219, U1.227, U1.237, U1.245, U1.253, U1.261
VDDGWT_RAW: C136.1, JMP9.2, L10.1
VDDGWT_U6: C133.1, JMP9.1, R28.2, U6.8
VDDPLL: C29.1, C62.1, C105.1, C126.1, C139.1, L8.2, TP21.1, TP23.1, U1.132, U1.279
VDDPLL_RAW: C128.1, JMP7.2, L8.1
VDDPLL_U5: C125.1, JMP7.1, R27.2, U5.8
VDDPST: C3.1, C6.1, C9.1, C28.1, C36.1, C39.1, C42.1, C61.1, C97.1, C117.1, C118.1, C130.1, L6.2, TP10.1, TP15.1, U1.13, U1.29, U1.43, U1.127, U1.160, U1.176, U1.190, U1.274
VDD_RAW: C83.1, C93.1, C116.1, JMP4.2, JMP4.4, L3.1, L6.1
VDD_U3: C88.1, C89.1, C90.1, C91.1, D1.1, JMP4.1, JMP4.3, R23.2, U3.1, U3.19, U3.20
Vin_1p4_U3: C81.1, C82.1, D1.2, JMP10.3, L2.2, U3.15, U3.16, U3.17, U12.D
Vin_1p4_U4: C100.1, C101.1, D2.2, L4.2, U4.15, U4.16, U4.17
Vin_1p4_U5: C124.1, L7.2, U5.1
Vin_1p4_U6: C132.1, L9.2, U6.1
Vin_1p4_analog: C99.1, J2.2, L4.1, R29.2
Vin_1p4_dig: C80.1, C123.1, C131.1, J2.4, L2.1, L7.1, L9.1, R29.1
Vin_3p3_raw: J2.6, JMP1.1
high_voltage_bias: HV1.1, TP1.1
